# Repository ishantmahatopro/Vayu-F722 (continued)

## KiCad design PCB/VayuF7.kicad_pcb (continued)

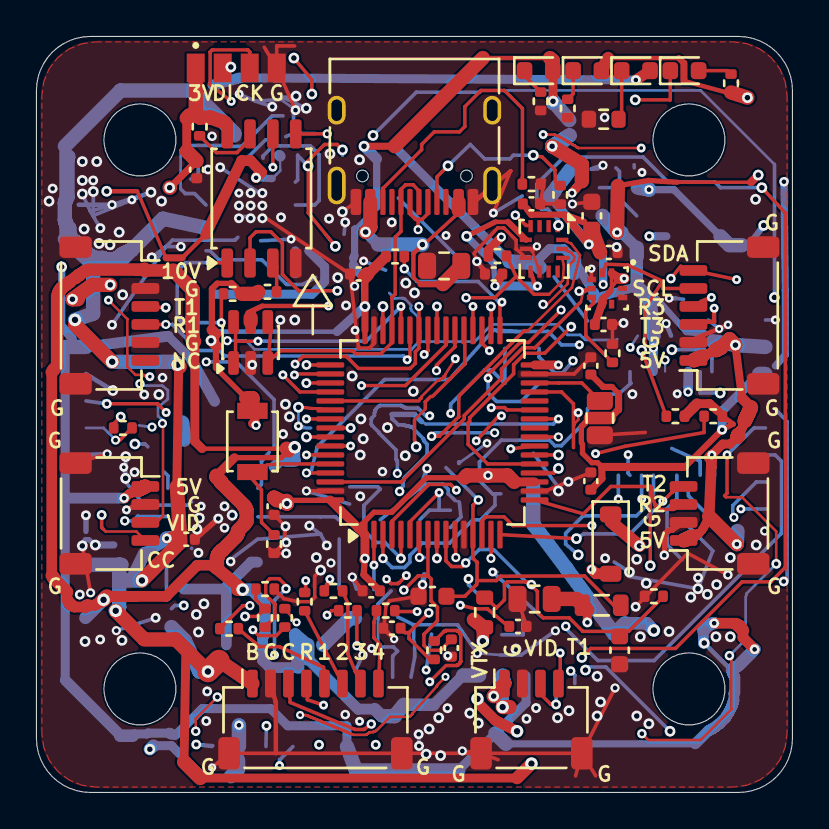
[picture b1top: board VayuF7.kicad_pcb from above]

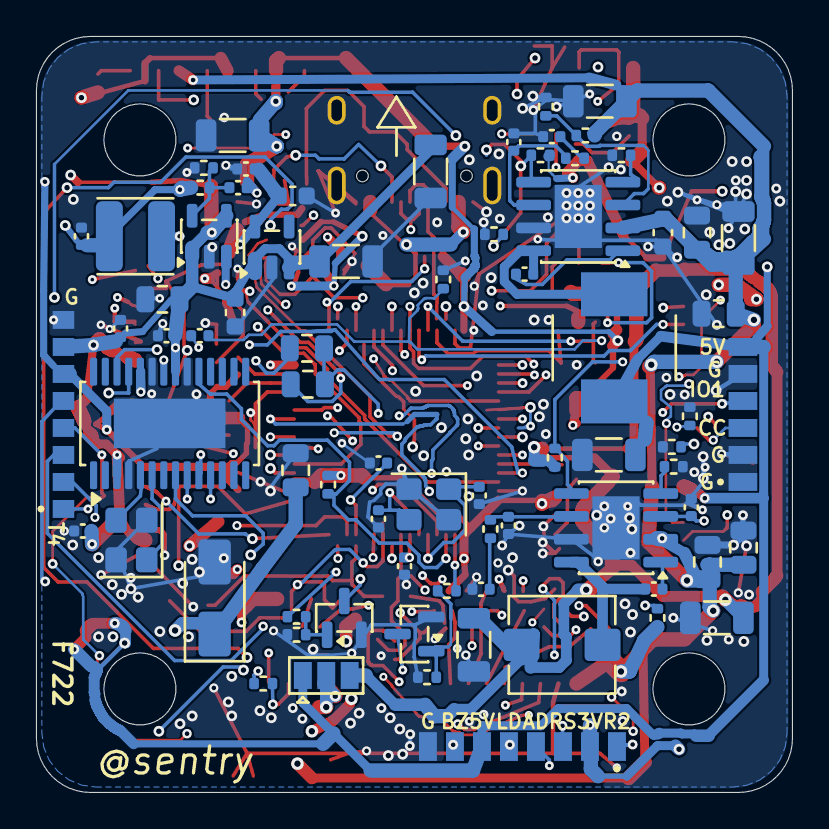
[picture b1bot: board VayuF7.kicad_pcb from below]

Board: 4 copper layers, 42.0 x 42.0 mm, 146 parts (75 on the bottom side), 105 nets.

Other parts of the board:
MH1, MH2, MH3, MH4: MountingHole_4mm

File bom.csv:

Designator,Footprint,Quantity,Value,LCSC Part #
"C1, C2",1206,2,4.7uF/50V,C29823
"C10, C14, C15, C17, C8, C9",1206,6,22uF/25V,C12891
"C11, C5",0402,2,100nF/16V,C1525
"C12, C60",0402,2,2.2nF,C1531
C13,0402,1,22pF,C106203
"C16, C34",0805,2,10uF/16V,C3039694
"C18, C21, C23, C24, C25, C26, C27, C30, C33, C35, C37, C38, C39, C40, C41, C42, C43, C46, C50, C51, C56, C58",0402,22,100nF/50V,C307331
"C19, C20, C22, C49",0603,4,1uF/50V,C5199872
"C28, C29",0805,2,4.7uF/16V,C2885646
"C3, C52, C53, C54, C55",0805,5,4.7uF/50V,C437557
"C31, C32",0402,2,15pF,C107004
C36,0603,1,2.2uF/16V,C415535
C4,0603,1,100nF/50V,C14663
"C47, C48",0805,2,22uF/16V,C45783
C59,0402,1,6.8pF,C189470
C6,0402,1,1.8nF,C107024
C7,0402,1,27pF,C107002
D1,D_SMA,1,SMAJ33A,C908777
D4,D_SOD-123,1,B5819W,C64885
D5,0603,1,RED 3V3,C2286
D6,0603,1,GREEN 5V,C965804
D7,0603,1,YELLOW VBAT,C965802
D8,0603,1,BLUE STATUS,C965807
FB1,0805,1,600R@100MHz 2A,C1017
J1,JST_SH_SM08B-SRSS-TB_1x08-1MP_P1.00mm_Horizontal,1,ESC 8P,C160407
J2,JST_SH_SM06B-SRSS-TB_1x06-1MP_P1.00mm_Horizontal,1,HD VTX 6P,C53055322
J3,JST_SH_SM04B-SRSS-TB_1x04-1MP_P1.00mm_Horizontal,1,RX 4P,C160404
J4,JST_SH_SM06B-SRSS-TB_1x06-1MP_P1.00mm_Horizontal,1,GPS/I2C 6P,C53055322
J5,JST_SH_SM04B-SRSS-TB_1x04-1MP_P1.00mm_Horizontal,1,CAM 4P,C160404
J6,JST_SH_SM04B-SRSS-TB_1x04-1MP_P1.00mm_Horizontal,1,VTX 4P,C160404
J8,USB_C_Receptacle_HRO_TYPE-C-31-M-12,1,USB-C 16P,C165948
L1,L_cjiang_FXL0630,1,6.8uH FXL0630-6R8-M,C167221
L2,L_Bourns_SRP5030T,1,10uH SRP5030T-100M,C189932
L3,L_Sunlord_SWPA4018S,1,2.2uH SWPA4018S2R2MT,C50543
Q1,SOT-23,1,2N7002,C8545
Q2,SOT-23,1,AO3400A,C20917
"R1, R7",0402,2,294k,C159047
R10,0402,1,118k,C25748
"R11, R5",0402,2,10.2k,C5153958
R12,0402,1,31.6k,C2998091
"R13, R14, R20, R28, R34, R35, R36, R37, R38, R50",0402,10,10k,C25744
"R16, R17",0402,2,5.1k,C25905
"R18, R19, R25, R26, R39",0402,5,2.2k,C25879
"R2, R8",0402,2,57.6k,C2960799
"R21, R22",0402,2,75R,C2909384
R23,0603,1,10k,C25804
"R24, R30, R33, R40, R41",0402,5,1k,C11702
"R27, R49",0402,2,100k,C25741
R29,0402,1,100R,C22369194
R3,0402,1,180k,C2909325
R31,0402,1,1.5k,C25867
R32,0603,1,15k,C22809
R4,0402,1,53.6k,C53398
"R42, R43, R44, R45, R47",0402,5,33R,C2906868
R48,0402,1,453k,C3013172
R6,0402,1,25.5k,C2998160
R9,0402,1,110k,C2909311
SW1,SW_SPST_B3U-1000P,1,BOOT,C231329
"U1, U2",SOIC-8-1EP_3.9x4.9mm_P1.27mm_EP2.62x3.51mm,2,AP64350SP-13,C2071691
U10,HTSSOP-28-1EP_4.4x9.7mm_P0.65mm_EP2.75x6.2mm,1,AT7456E,C82351
U3,SOT-23-5,1,TLV62569DBVR,C141836
U4,SOT-23-5,1,LP5907MFX-3.3,C80670
U5,LQFP-64_10x10mm_P0.5mm,1,STM32F722RET6,C118207
U6,SOT-23-6,1,USBLC6-2SC6,C2687116
U7,Bosch_LGA-14_3x2.5mm_P0.5mm,1,ICM-42688-P,C1850418
U8,Bosch_LGA-10_2x2mm_BMP388_BMP390,1,BMP388,C779278
U9,SOIC-8_5.3x5.3mm_P1.27mm,1,W25Q128JVSIQ,C97521
X1,Crystal_SMD_3225-4Pin_3.2x2.5mm,1,8MHz X32258MOB4SI 12pF,C2682775
X2,Crystal_SMD_3225-4Pin_3.2x2.5mm,1,27MHz X322527MSB4SI,C9008

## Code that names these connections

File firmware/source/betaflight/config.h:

#pragma once

#define TARGET_NAME "VAYUF7"
#define USE_TARGET_VAYUF7

#define MCU_STM32F722
#define TARGET_BOARD_IDENTIFIER "VAYUF7"

#define USE_ACC
#define USE_GYRO
#define USE_BARO
#define USE_FLASH
#define USE_OSD
#define USE_MAG
#define USE_RANGEFINDER

#define USE_ACC_SPI_ICM42688P
#define USE_GYRO_SPI_ICM42688P
#define USE_BARO_BMP388
#define USE_FLASH_W25Q128
#define USE_OSD_AT7456E

#define USE_UART1
#define USE_UART2
#define USE_UART3
#define USE_UART4
#define USE_UART5
#define USE_UART6

#define USE_SPI1
#define USE_SPI2
#define USE_SPI3
#define USE_I2C1

#define TARGET_RX_SPI_NONE

/* STM32F722RET6 pin mapping for the Vayu F7 board */
#define LED0_PIN PINC13
#define BEEPER_PIN PINB12
#define BIND_BUTTON_PIN PINB2
#define SDCARD_DETECT_PIN NONE

/* SPI1: ICM-42688-P */
#define SPI1_SCK_PIN PINA5
#define SPI1_MISO_PIN PINA6
#define SPI1_MOSI_PIN PINA7
#define SPI1_NSS_PIN PINA4

/* SPI2: AT7456E OSD */
#define SPI2_SCK_PIN PINB13
#define SPI2_MISO_PIN PINB14
#define SPI2_MOSI_PIN PINB15
#define SPI2_NSS_PIN PINB12

/* SPI3: W25Q128 blackbox flash */
#define SPI3_SCK_PIN PINB3
#define SPI3_MISO_PIN PINB4
#define SPI3_MOSI_PIN PINB5
#define SPI3_NSS_PIN PINA15

/* I2C1: BMP388 */
#define I2C1_SCL_PIN PINB8
#define I2C1_SDA_PIN PINB9

/* UART1: telemetry / RX */
#define UART1_TX_PIN PINA9
#define UART1_RX_PIN PINA10

/* UART2: GPS / serial RX */
#define UART2_TX_PIN PINA2
#define UART2_RX_PIN PINA3

/* UART3: ESC telemetry / external serial */
#define UART3_TX_PIN PINB10
#define UART3_RX_PIN PINB11

/* UART4: pads / RX / debug */
#define UART4_TX_PIN PINA0
#define UART4_RX_PIN PINA1

/* UART5: pads / additional serial */
#define UART5_TX_PIN PINC12
#define UART5_RX_PIN PIND2

/* UART6: extra serial / VTX or telemetry */
#define UART6_TX_PIN PINC6
#define UART6_RX_PIN PINC7

/* Motor outputs: timer-backed DShot-capable outputs */
#define MOTOR1_PIN PINA8
#define MOTOR2_PIN PINA9
#define MOTOR3_PIN PINA10
#define MOTOR4_PIN PINA11

#define MOTOR1_TIMER TIM1
#define MOTOR2_TIMER TIM1
#define MOTOR3_TIMER TIM1
#define MOTOR4_TIMER TIM1

#define MOTOR1_TIMER_CHNL 1
#define MOTOR2_TIMER_CHNL 2
#define MOTOR3_TIMER_CHNL 3
#define MOTOR4_TIMER_CHNL 4

#define ADC_CHANNEL_1_PIN PINA0
#define ADC_CHANNEL_2_PIN PINA1
#define ADC_CHANNEL_3_PIN PINA2
#define ADC_CHANNEL_4_PIN PINA3

#define DEFAULT_RX_TYPE RX_TYPE_SERIAL
#define SERIAL_PORT_COUNT 6

#define VTX_POWER_PIN PINB0
#define VTX_ENABLE_PIN PINB1

#define PINIO1_PIN NONE
#define PINIO2_PIN NONE

#define USE_DSHOT
#define USE_DSHOT_BITBANG

#define USE_ESC_SENSOR

#define USE_LED_STRIP
#define USE_OSD

#define USE_TINYGPS
#define USE_GPS
#define USE_GPS_PROTO_UBLOX

#define TARGET_HAS_BEEPER
#define TARGET_HAS_OSD
#define TARGET_HAS_FLASH

#define DEFAULT_FEATURES FEATURE_TX_PROF_SEL

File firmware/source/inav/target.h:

#pragma once

#define TARGET_BOARD_IDENTIFIER "VAYUF7"
#define USE_TARGET_VAYUF7
#define USE_ACC
#define USE_GYRO
#define USE_BARO
#define USE_FLASH
#define USE_OSD
#define USE_MAG
#define USE_PWM_OUTPUT
#define USE_DSHOT

#define TARGET_MCU STM32F722xx

#define USE_SPI
#define USE_SPI_DEVICE_1
#define USE_SPI_DEVICE_2
#define USE_SPI_DEVICE_3
#define USE_I2C
#define USE_I2C_DEVICE_1

#define USE_UART1
#define USE_UART2
#define USE_UART3
#define USE_UART4
#define USE_UART5
#define USE_UART6

/* Sensor mapping for the Vayu F7 board */
#define ACC_SPI_INSTANCE SPI1
#define GYRO_SPI_INSTANCE SPI1
#define OSD_SPI_INSTANCE SPI2
#define FLASH_SPI_INSTANCE SPI3
#define BARO_I2C_INSTANCE I2C1

/* GPIO mapping: realistic board assignments for the Vayu F7 hardware */
#define ACC_CS_PIN GPIO_PIN_4
#define GYRO_CS_PIN GPIO_PIN_4
#define FLASH_CS_PIN GPIO_PIN_15
#define OSD_CS_PIN GPIO_PIN_12

#define SPI1_SCK_PIN GPIO_PIN_5
#define SPI1_MISO_PIN GPIO_PIN_6
#define SPI1_MOSI_PIN GPIO_PIN_7

#define SPI2_SCK_PIN GPIO_PIN_13
#define SPI2_MISO_PIN GPIO_PIN_14
#define SPI2_MOSI_PIN GPIO_PIN_15

#define SPI3_SCK_PIN GPIO_PIN_3
#define SPI3_MISO_PIN GPIO_PIN_4
#define SPI3_MOSI_PIN GPIO_PIN_5

#define I2C1_SCL_PIN GPIO_PIN_8
#define I2C1_SDA_PIN GPIO_PIN_9

#define UART1_TX_PIN GPIO_PIN_9
#define UART1_RX_PIN GPIO_PIN_10
#define UART2_TX_PIN GPIO_PIN_2
#define UART2_RX_PIN GPIO_PIN_3
#define UART3_TX_PIN GPIO_PIN_10
#define UART3_RX_PIN GPIO_PIN_11
#define UART4_TX_PIN GPIO_PIN_0
#define UART4_RX_PIN GPIO_PIN_1

#define MOTOR_OUTPUT_1 GPIO_PIN_8
#define MOTOR_OUTPUT_2 GPIO_PIN_9
#define MOTOR_OUTPUT_3 GPIO_PIN_10
#define MOTOR_OUTPUT_4 GPIO_PIN_11

void targetInit(void);
void targetConfigureMotorOutputs(void);

#ifndef __cplusplus
extern "C" {
#endif

extern void initBoardHardware(void);
extern void motorConfig;

#ifndef __cplusplus
}
#endif
